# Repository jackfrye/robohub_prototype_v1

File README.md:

# robohub_prototype_v1
ATSAMA based board for command and control of future robotics systems

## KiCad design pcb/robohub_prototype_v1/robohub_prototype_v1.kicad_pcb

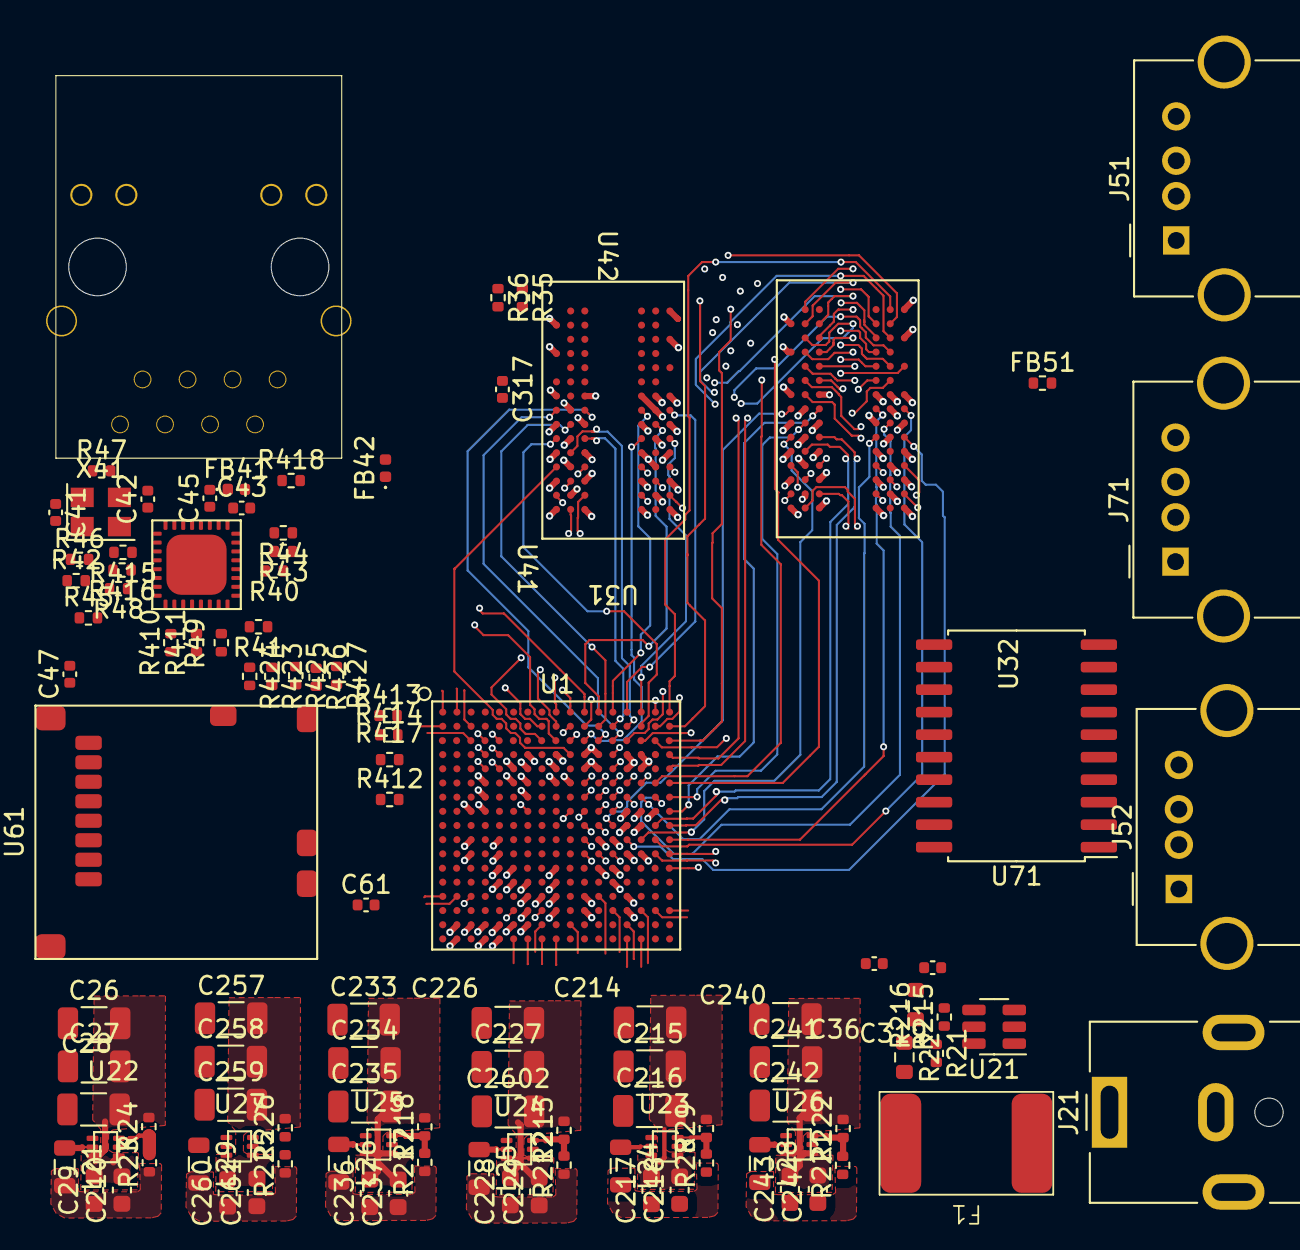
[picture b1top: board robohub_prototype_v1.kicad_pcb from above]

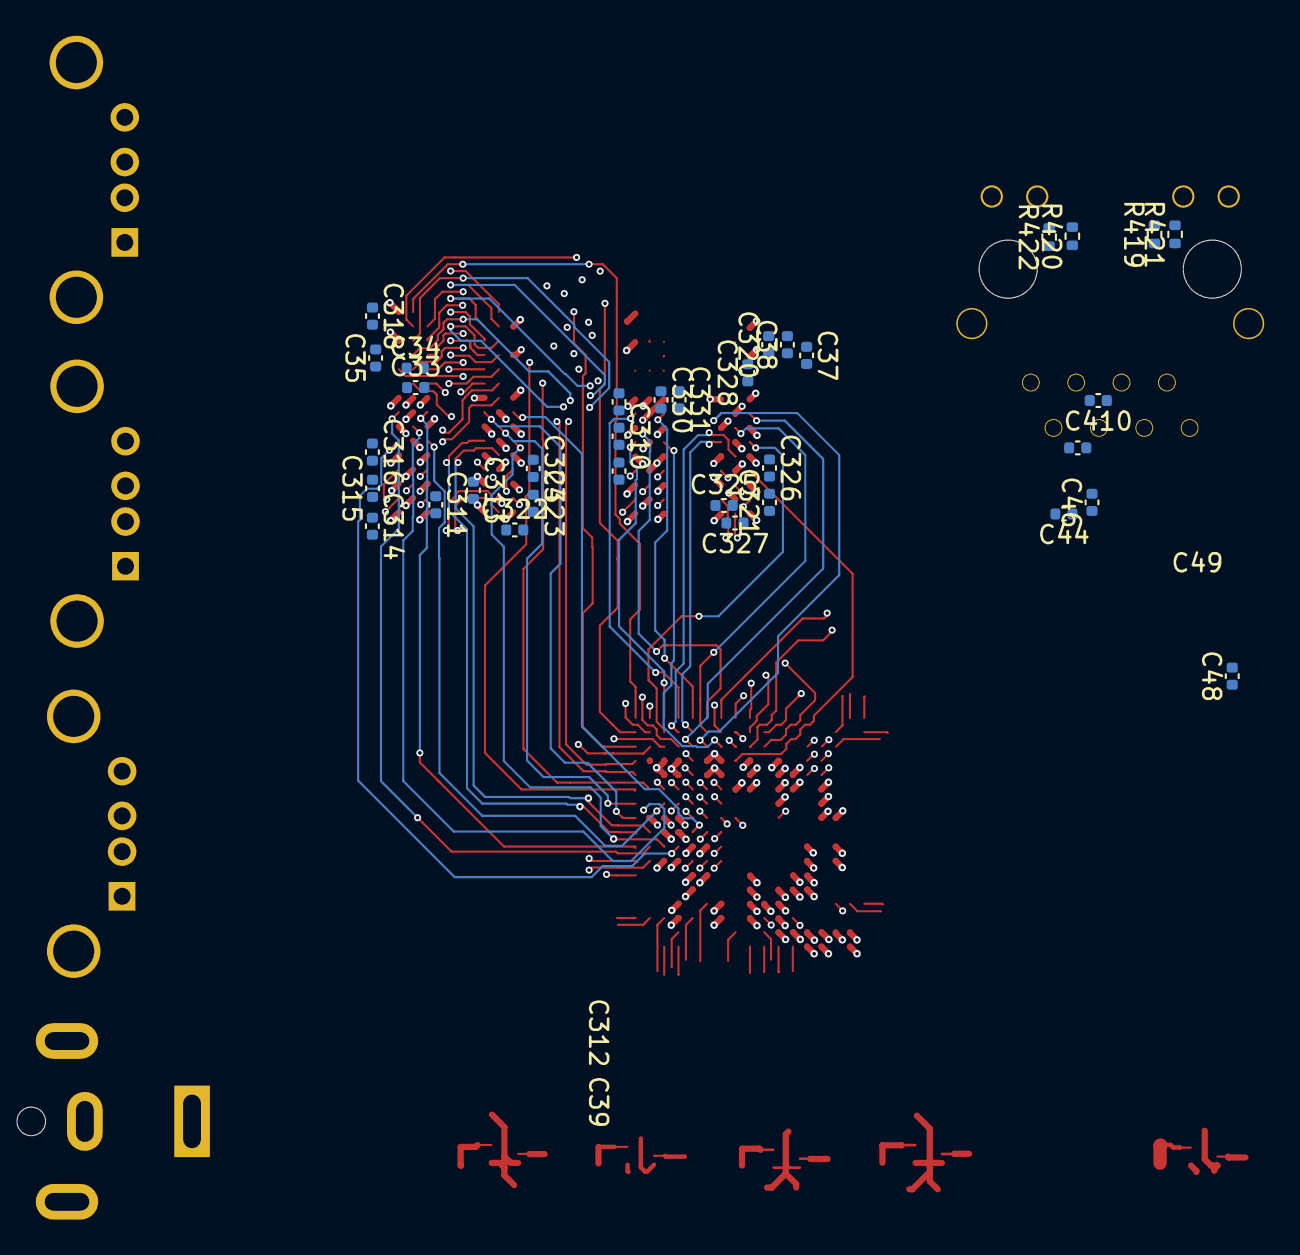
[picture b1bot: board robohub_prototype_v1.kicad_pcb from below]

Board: 10 copper layers, 144 parts (34 on the bottom side), 150 nets.

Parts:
C26, C27, C214, C215, C226, C227, C233, C234, C240, C241, C257, C258: 10u; C_1206_3216Metric
C28, C216, C235, C242, C259, C2602: 0.1u; C_1206_3216Metric
C29, C210, C217, C218, C228, C229, C236, C237, C243, C244, C260, C261: 22u; C_0603_1608Metric
C33, C38, C39, C44, C46, C48, C49, C310, C311, C312, C313, C320, C321, C322, C323, C324, C325, C330, C410: 100n; C_0402_1005Metric
C34, C314, C315, C316, C326, C327, C328: 1n; C_0402_1005Metric
C35, C45, C47, C61, C317: 10u; C_0402_1005Metric
C36, C37, C318, C319: 1u; C_0402_1005Metric
C41, C42: 22p; C_0402_1005Metric
C43: 2u2; C_0402_1005Metric
C331: 100nf; C_0402_1005Metric
F1: Fuse; 0ZCF0050FF2C
FB41, FB42: FerriteBead; D_0402_1005Metric
FB51: FerriteBead; R_0402_1005Metric
J21: Barrel_Jack_Switch_Pin3Ring; BarrelJack_CUI_PJ-063AH_Horizontal
J51, J52, J71: USB_A; USB_A_Molex_67643_Horizontal
L21, L24, L25: 2.2u; L_0805_2012Metric
L26, L28, L29: 1u; L_0805_2012Metric
R21, R23, R28, R35, R36, R212, R215: 100k; R_0402_1005Metric
R22, R216: 36.5k; R_0603_1608Metric
R24, R29, R213: 22.1k; R_0402_1005Metric
R40, R43, R44, R45, R46, R423, R424, R425, R426, R427: 10K; R_0402_1005Metric
R41, R42: 1K; R_0402_1005Metric
R47: DNP; R_0402_1005Metric
R48, R49, R410, R412, R413, R414, R415, R416, R417: 22; R_0402_1005Metric
R217, R218, R222, R226, R419, R420: 10k; R_0402_1005Metric
R221: 20k; R_0402_1005Metric
R225: 32k; R_0402_1005Metric
R411: 39; R_0402_1005Metric
R418: 6k4; R_0402_1005Metric
R421, R422: 510; R_0402_1005Metric
U1: ATSAMA5D27C
U21: LM3880; SOT-23-6
U22, U23, U24, U25, U26, U27: TPS564242DRL; TPS564247DRLR
U31, U32: W972GG6KB-25
U41: KSZ8081RNB
U42: SI-60110-F
U61: molex_5025700893
U71: MCP2200-I-SO; SOIC-20W_7.5x12.8mm_P1.27mm
X41: ECS-2520MV-xxx-xx; Oscillator_SMD_Abracon_ASE-4Pin_3.2x2.5mm

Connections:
5V: C26.1, C27.1, C28.1, C214.1, C215.1, C216.1, C226.1, C227.1, C233.1, C234.1, C235.1, C240.1, C241.1, C242.1, C257.1, C258.1, C259.1, C2602.1, F1.2, FB51.2, U21.1 (VCC), U21.3 (EN), U22.1 (VIN), U23.1 (VIN), U24.1 (VIN), U25.1 (VIN), U26.1 (VIN), U27.1 (VIN)
/DDR2_3/DDR_A0: U1.F12 (DDR_A0), U31.M8 (A0), U32.M8 (A0)
/DDR2_3/DDR_A1: U1.C17 (DDR_A1), U31.M3 (A1), U32.M3 (A1)
/DDR2_3/DDR_A2: U1.B17 (DDR_A2), U31.M7 (A2), U32.M7 (A2)
/DDR2_3/DDR_A3: U1.B16 (DDR_A3), U31.N2 (A3), U32.N2 (A3)
/DDR2_3/DDR_A4: U1.C16 (DDR_A4), U31.N8 (A4), U32.N8 (A4)
/DDR2_3/DDR_A5: U1.G14 (DDR_A5), U31.N3 (A5), U32.N3 (A5)
/DDR2_3/DDR_A6: U1.F14 (DDR_A6), U31.N7 (A6), U32.N7 (A6)
/DDR2_3/DDR_A7: U1.F11 (DDR_A7), U31.P2 (A7), U32.P2 (A7)
/DDR2_3/DDR_A8: U1.C14 (DDR_A8), U31.P8 (A8), U32.P8 (A8)
/DDR2_3/DDR_A9: U1.D13 (DDR_A9), U31.P3 (A9), U32.P3 (A9)
/DDR2_3/DDR_A10: U1.C15 (DDR_A10), U31.M2 (A10), U32.M2 (A10)
/DDR2_3/DDR_A11: U1.A16 (DDR_A11), U31.P7 (A11), U32.P7 (A11)
/DDR2_3/DDR_A12: U1.A17 (DDR_A12), U31.R2 (A12), U32.R2 (A12)
/DDR2_3/DDR_A13: U1.G11 (DDR_A13), U31.R8 (A13), U32.R8 (A13)
/DDR2_3/DDR_BA0: U1.H12 (DDR_BA0), U31.L2 (BA0), U32.L2 (BA0)
/DDR2_3/DDR_BA1: U1.H13 (DDR_BA1), U31.L3 (BA1), U32.L3 (BA1)
/DDR2_3/DDR_BA2: U1.F17 (DDR_DA2), U31.L1 (BA2), U32.L1 (BA2)
/DDR2_3/DDR_CAS: U1.G12 (DDR_CAS), U31.L7 (~CAS), U32.L7 (~CAS)
/DDR2_3/DDR_CKE: R36.1, U1.F16 (DDR_CKE), U31.K2 (CKE), U32.K2 (CKE)
/DDR2_3/DDR_CLK+: U1.E17 (DDR_CLK), U31.J8 (CK_P), U32.J8 (CK_P)
/DDR2_3/DDR_CLK-: U1.D17 (DDR_CLKN), U31.K8 (CK_N), U32.K8 (CK_N)
/DDR2_3/DDR_CS: U1.G13 (DDR_CS), U31.L8 (~CS), U32.L8 (~CS)
/DDR2_3/DDR_D0: U1.B12 (DDR_D0), U31.G8 (DQ0)
/DDR2_3/DDR_D1: U1.A12 (DDR_D1), U31.G2 (DQ1)
/DDR2_3/DDR_D2: U1.C12 (DDR_D2), U31.H7 (DQ2)
/DDR2_3/DDR_D3: U1.A13 (DDR_D3), U31.H3 (DQ3)
/DDR2_3/DDR_D4: U1.A14 (DDR_D4), U31.H1 (DQ4)
/DDR2_3/DDR_D5: U1.C13 (DDR_D5), U31.H9 (DQ5)
/DDR2_3/DDR_D6: U1.A15 (DDR_D6), U31.F1 (DQ6)
/DDR2_3/DDR_D7: U1.B15 (DDR_D7), U31.F9 (DQ7)
/DDR2_3/DDR_D8: U1.G17 (DDR_D8), U32.G8 (DQ0)
/DDR2_3/DDR_D9: U1.G16 (DDR_D9), U32.G2 (DQ1)
/DDR2_3/DDR_D10: U1.H17 (DDR_D10), U32.H7 (DQ2)
/DDR2_3/DDR_D11: U1.K17 (DDR_D11), U32.H3 (DQ3)
/DDR2_3/DDR_D12: U1.K16 (DDR_D12), U32.H1 (DQ4)
/DDR2_3/DDR_D13: U1.J13 (DDR_D13), U32.H9 (DQ5)
/DDR2_3/DDR_D14: U1.K14 (DDR_D14), U32.F1 (DQ6)
/DDR2_3/DDR_D15: U1.K15 (DDR_D15), U32.F9 (DQ7)
/DDR2_3/DDR_D16: U1.B8 (DDR_D16), U31.C8 (DQ8)
/DDR2_3/DDR_D17: U1.B9 (DDR_D17), U31.C2 (DQ9)
/DDR2_3/DDR_D18: U1.C9 (DDR_D18), U31.D7 (DQ10)
/DDR2_3/DDR_D19: U1.A9 (DDR_D19), U31.D3 (DQ11)
/DDR2_3/DDR_D20: U1.A10 (DDR_D20), U31.D1 (DQ12)
/DDR2_3/DDR_D21: U1.D10 (DDR_D21), U31.D9 (DQ13)
/DDR2_3/DDR_D22: U1.B11 (DDR_D22), U31.B1 (DQ14)
/DDR2_3/DDR_D23: U1.A11 (DDR_D23), U31.B9 (DQ15)
/DDR2_3/DDR_D24: U1.J12 (DDR_D24), U32.C8 (DQ8)
/DDR2_3/DDR_D25: U1.H10 (DDR_D25), U32.C2 (DQ9)
/DDR2_3/DDR_D26: U1.J11 (DDR_D26), U32.D7 (DQ10)
/DDR2_3/DDR_D27: U1.K11 (DDR_D27), U32.D3 (DQ11)
/DDR2_3/DDR_D28: U1.L13 (DDR_D28), U32.D1 (DQ12)
/DDR2_3/DDR_D29: U1.L11 (DDR_D29), U32.D9 (DQ13)
/DDR2_3/DDR_D30: U1.L12 (DDR_D30), U32.B1 (DQ14)
/DDR2_3/DDR_D31: U1.M17 (DDR_D31), U32.B9 (DQ15)
/DDR2_3/DDR_DQM0: U1.C11 (DDR_DQM0), U31.F3 (LDM)
/DDR2_3/DDR_DQM1: U1.G15 (DDR_DQM1), U32.F3 (LDM)
/DDR2_3/DDR_DQM2: U1.C8 (DDR_DQM2), U31.B3 (UDM)
/DDR2_3/DDR_DQM3: U1.H11 (DDR_DQM3), U32.B3 (UDM)
/DDR2_3/DDR_DQS0+: U1.B13 (DDR_DQS0), U31.F7 (LDQS_P)
/DDR2_3/DDR_DQS0-: U1.B14 (DDR_DQSN0), U31.E8 (NU/LDQS_N)
/DDR2_3/DDR_DQS1+: U1.J17 (DDR_DQS1), U32.F7 (LDQS_P)
/DDR2_3/DDR_DQS1-: U1.J16 (DDR_DQSN1), U32.E8 (NU/LDQS_N)
/DDR2_3/DDR_DQS2+: U1.C10 (DDR_DQS2), U31.B7 (UDQS_P)
/DDR2_3/DDR_DQS2-: U1.B10 (DDR_DQSN2), U31.A8 (NU/UDQS_N)
/DDR2_3/DDR_DQS3+: U1.L17 (DDR_DQS3), U32.B7 (UDQS_P)
/DDR2_3/DDR_DQS3-: U1.L16 (DDR_DQSN3), U32.A8 (NU/UDQS_N)
/DDR2_3/DDR_RAS: U1.F13 (DDR_RAS), U31.K7 (~RAS), U32.K7 (~RAS)
/DDR2_3/DDR_WE: U1.F15 (DDR_WE), U31.K3 (~WE), U32.K3 (~WE)
/Ethernet_MAC_4/CT1: C49.1, U42.4 (CT)
/Ethernet_MAC_4/CT2: C410.1, U42.5 (CT)
/Ethernet_MAC_4/ETH_COL_CONFI2: R40.2, U41.28 (COL/CONFIG0)
/Ethernet_MAC_4/ETH_CRS_CONFI1: R427.1, U41.29 (CRS/CONFIG1)
/Ethernet_MAC_4/ETH_LED0: R43.2, R419.2, U41.30 (LED0/NWAYEN), U42.11 (LED0)
/Ethernet_MAC_4/ETH_LED1: R44.2, R420.2, U41.31 (LED1/SPEED), U42.10 (LED1)
/Ethernet_MAC_4/ETH_RXC_BC: R411.1, U41.19 (RXC/B_CAST_OFF)
/Ethernet_MAC_4/ETH_RXD0_DUPLEX: R45.2, U41.16 (RXD0/DUPLEX)
/Ethernet_MAC_4/ETH_RXD1_PHYAD2: R48.1, R423.1, U41.15 (RXD1/PHYAD2)
/Ethernet_MAC_4/ETH_RXD2_PHYAD1: R426.1, U41.14 (RXD2/PHYAD1)
/Ethernet_MAC_4/ETH_RXD3_PHYAD0: R46.2, U41.13 (RXD3/PHYAD0)
/Ethernet_MAC_4/ETH_RXDIV_CONFIG2: R410.1, R425.1, U41.18 (RXDIV/CONFIG2)
/Ethernet_MAC_4/ETH_RXER_ISO: R49.1, R424.1, U41.20 (RXER/ISO)
/Ethernet_MAC_4/ETH_TX_D0: R413.1, U41.24 (TXD0)
/Ethernet_MAC_4/ETH_TX_D1: R412.1, U41.25 (TXD1)
/Ethernet_MAC_4/ETH_TX_EN: R414.1, U41.23 (TXEN)
/Ethernet_MAC_4/ETH_XI: C41.2, R47.1, U41.9 (XI), X41.1 (Tri-State)
/Ethernet_MAC_4/ETH_XO: C42.2, R47.2, U41.8 (X0), X41.3 (OUT)
/Ethernet_MAC_4/LED0_PWR: R421.2, U42.12 (LED0_PWR)
/Ethernet_MAC_4/LED1_PWR: R422.2, U42.9 (LED1_PWR)
/Ethernet_MAC_4/MDC: R416.1, U41.12 (MDC)
/Ethernet_MAC_4/MDIO: R42.2, R415.1, U41.11 (MDIO)
/Ethernet_MAC_4/REXT: R418.2, U41.10 (REXT)
/Ethernet_MAC_4/RXM: U41.4 (RXM), U42.6 (RD-)
/Ethernet_MAC_4/RXP: U41.5 (RXP), U42.3 (RD+)
/Ethernet_MAC_4/TXM: U41.6 (TXM), U42.2 (TD-)
/Ethernet_MAC_4/TXP: U41.7 (TXP), U42.1 (TD+)
/Ethernet_MAC_4/VDDA_3V3: C45.1, C46.1, FB41.1, U41.3 (VDDA_3V3)
/Ethernet_MAC_4/~INTRP_NAND: R41.2, R417.1, U41.21 (~INTRP/NAND)
/Power Managment_2/PS_GRP1_EN: R21.1, U21.6 (FLAG1)
/Power Managment_2/PS_GRP1_EN_DIV: R21.2, R22.1, U22.5 (EN), U23.5 (EN), U24.5 (EN), U26.5 (EN)
/Power Managment_2/PS_GRP2_EN: R215.1, U21.5 (FLAG2)
/Power Managment_2/PS_GRP2_EN_DIV: R215.2, R216.1, U25.5 (EN), U27.5 (EN)
/Power Managment_2/VCC_1_2_DDR_FB: R221.2, R222.1, U26.6 (FB)
/Power Managment_2/VCC_1_2_DDR_SW: L28.1, U26.2 (SW)
/Power Managment_2/VCC_1_2_FB: R217.2, R218.1, U25.6 (FB)
/Power Managment_2/VCC_1_2_SW: L26.1, U25.2 (SW)
/Power Managment_2/VCC_3_3_A_FB: R23.2, R24.1, U22.6 (FB)
/Power Managment_2/VCC_3_3_A_SW: L21.1, U22.2 (SW)
/Power Managment_2/VCC_3_3_B_FB: R28.2, R29.1, U23.6 (FB)
/Power Managment_2/VCC_3_3_B_SW: L24.1, U23.2 (SW)
/Power Managment_2/VCC_3_3_C_FB: R212.2, R213.1, U24.6 (FB)
/Power Managment_2/VCC_3_3_C_SW: L25.1, U24.2 (SW)
/UART_7/D+: J71.3 (D+), U71.19 (D+)
/UART_7/D-: J71.2 (D-), U71.18 (D-)
/UART_7/VDD: J71.1 (VBUS), U71.1 (VDD), U71.13 (CTS)
CH_GND: FB42.1, U42.8 (CH_GND), U42.13 (CH_GND), U42.14 (CH_GND)
DDR_VREF: C33.1, C34.1, C330.1, C331.1, U1.D16 (DDR_VREF), U1.H16 (DDR_VREF), U31.J2 (VREF), U32.J2 (VREF)
GND: C26.2, C27.2, C28.2, C29.2, C33.2, C34.2, C35.2, C36.2, C37.2, C38.2, C39.2, C41.1, C42.1, C43.2, C44.2, C45.2, C46.2, C47.2, C48.2, C49.2, C61.2, C210.2, C214.2, C215.2, C216.2, C217.2, C218.2, C226.2, C227.2, C228.2, C229.2, C233.2, C234.2, C235.2, C236.2, C237.2, C240.2, C241.2, C242.2, C243.2, C244.2, C257.2, C258.2, C259.2, C260.2, C261.2, C310.2, C311.2, C312.2, C313.2, C314.2, C315.2, C316.2, C317.2, C318.2, C319.2, C320.2, C321.2, C322.2, C323.2, C324.2, C325.2, C326.2, C327.2, C328.2, C330.2, C331.2, C410.2, C2602.2, FB42.2, J21.2, J51.4 (GND), J52.4 (GND), J71.4 (GND), R22.2, R24.2, R29.2, R36.2, R213.2, R216.2, R218.2, R222.2, R226.2, R418.1, R423.2, R424.2, R425.2, R426.2, R427.2, U1.D14 (GNDIODDR), U1.E7 (GNDCORE), U1.E9 (GNDCORE), U1.E11 (GNDIODDR), U1.E12 (GNDIODDR), U1.E14 (GNDIODDR), U1.F6 (GNDIOP0), U1.F9 (GNDIOP2), U1.G4 (GNDISC), U1.G7 (GNDIOP0), U1.H4 (GNDCORE), U1.H14 (GNDIODDR), U1.J14 (GNDIODDR), U1.K5 (GNDANA), U1.K12 (GNDCORE), U1.L3 (GNDANA), U1.L14 (GNDIODDR), U1.M5 (GNDCORE), U1.M9 (GNDCORE), U1.M13 (GNDIOP1), U1.N6 (GNDBU), U1.P9 (GNDUTMII), U1.P14 (GNDIOP1), U1.R7 (GNDUTMIC), U1.R11 (GNDSDMMC), U1.T4 (GNDAUDIOPLL), U1.T5 (GNDPLL), U1.T6 (GNDOSC), U1.U5 (GNDPLLA), U21.2 (GND), U22.3 (GND), U22.4 (AGND), U23.3 (GND), U23.4 (AGND), U24.3 (GND), U24.4 (AGND), U25.3 (GND), U25.4 (AGND), U26.3 (GND), U26.4 (AGND), U27.3 (GND), U27.4 (AGND), U31.A3 (VSS1), U31.A7 (VSSQ1), U31.B2 (VSSQ2), U31.B8 (VSSQ3), U31.D2 (VSSQ4), U31.D8 (VSSQ5), U31.E3 (VSS2), U31.E7 (VSSQ6), U31.F2 (VSSQ7), U31.F8 (VSSQ8), U31.H2 (VSSQ9), U31.H8 (VSSQ10), U31.J3 (VSS3), U31.J7 (VSSDL), U31.N1 (VSS4), U31.P9 (VSS5), U32.A3 (VSS1), U32.A7 (VSSQ1), U32.B2 (VSSQ2), U32.B8 (VSSQ3), U32.D2 (VSSQ4), U32.D8 (VSSQ5), U32.E3 (VSS2), U32.E7 (VSSQ6), U32.F2 (VSSQ7), U32.F8 (VSSQ8), U32.H2 (VSSQ9), U32.H8 (VSSQ10), U32.J3 (VSS3), U32.J7 (VSSDL), U32.N1 (VSS4), U32.P9 (VSS5), U41.1 (GND), U41.33 (PADDLE), U61.6 (VSS), U61.11 (SHELL), U61.12 (SHELL), U61.13 (SHELL), U61.14 (SHELL), U71.20 (VSS), X41.2 (GND), X41.4 (VDD)
unnamed: R35.2, U1.E16 (DDR_RESETN)
unnamed: R225.2, R226.1, U27.6 (FB)
unnamed: L29.1, U27.2 (SW)
PA18_SD_DAT0: U1.U14 (PA18), U61.7 (DAT0)
PA19_SD_DAT1: U1.T14 (PA19), U61.8 (DAT1)
PA20_SD_DAT2: U1.P12 (PA20), U61.1 (DAT2)
PA21_SD_DAT3: U1.R13 (PA21), U61.2 (CD/DAT3)
PB14_ETH_RXC_BC: R411.2, U1.C5 (PB14)
PB15_ETH_TX_EN: R414.2, U1.H7 (PB15)
PB16_ETH_RXDIV_CONFIG2: R410.2, U1.D5 (PB16)
PB17_ETH_RXER_ISO: R49.2, U1.C4 (PB17)
PB19_ETH_RXD1_PHYAD2: R48.2, U1.D4 (PB19)
PB20_ETH_TX_D0: R413.2, U1.B3 (PB20)
PB21_ETH_TX_D1: R412.2, U1.A2 (PB21)
PB22_MDC: R416.2, U1.C3 (PB22)
PB23_MDIO: R415.2, U1.A1 (PB23)
PB24_~INTRP_NAND: R417.2, U1.E5 (PB24)
PB26_UART_RX: U1.E4 (PB26), U71.12 (RX)
PB27_UART_TX: U1.B1 (PB27), U71.10 (TX)
SD_VDD: C61.1, C217.1, C218.1, L24.2, R28.1, U1.E6 (VDDIOP0), U1.F4 (VDDISC), U1.F7 (VDDIOP0), U1.F10 (VDDIOP2), U1.N13 (VDDIOP1), U1.P11 (VDDSDMMC), U1.R14 (VDDIOP1), U1.U2 (NRST), U61.4 (VDD)
USBA_5V: FB51.1, J51.1 (VBUS)
USBA_DM: J51.2 (D-), U1.R8 (HHSDMA)
USBA_DP: J51.3 (D+), U1.T8 (HHSDPA)
USBB_DM: J52.2 (D-), U1.U9 (HHSDMB)
USBB_DP: J52.3 (D+), U1.U8 (HHSDPB)
VCC: F1.1, J21.1
VCC_1_2: C43.1, C44.1, C236.1, C237.1, L26.2, R217.1, U1.D7 (VDDCORE), U1.D9 (VDDCORE), U1.H3 (VDDCORE), U1.K13 (VDDCORE), U1.N5 (VDDCORE), U1.N9 (VDDCORE), U1.P7 (VDDUTMIC), U1.R9 (VDDHSIC), U41.2 (VDD_1V2)
VCC_1_8_DDR: C35.1, C36.1, C37.1, C38.1, C39.1, C243.1, C244.1, C310.1, C311.1, C312.1, C313.1, C314.1, C315.1, C316.1, C317.1, C318.1, C319.1, C320.1, C321.1, C322.1, C323.1, C324.1, C325.1, C326.1, C327.1, C328.1, L28.2, R35.1, R221.1, U1.D11 (VDDIODDR), U1.D12 (VDDIODDR), U1.D15 (VDDIODDR), U1.E15 (VDDIODDR), U1.H15 (VDDIODDR), U1.J15 (VDDIODDR), U1.L15 (VDDIODDR), U31.A1 (VDD1), U31.A9 (VDDQ1), U31.C1 (VDDQ2), U31.C3 (VDDQ3), U31.C7 (VDDQ4), U31.C9 (VDDQ5), U31.E1 (VDD2), U31.E9 (VDDQ6), U31.G1 (VDDQ7), U31.G3 (VDDQ8), U31.G7 (VDDQ9), U31.G9 (VDDQ10), U31.J1 (VDDL), U31.J9 (VDD3), U31.M9 (VDD4), U31.R1 (VDD5), U32.A1 (VDD1), U32.A9 (VDDQ1), U32.C1 (VDDQ2), U32.C3 (VDDQ3), U32.C7 (VDDQ4), U32.C9 (VDDQ5), U32.E1 (VDD2), U32.E9 (VDDQ6), U32.G1 (VDDQ7), U32.G3 (VDDQ8), U32.G7 (VDDQ9), U32.G9 (VDDQ10), U32.J1 (VDDL), U32.J9 (VDD3), U32.M9 (VDD4), U32.R1 (VDD5)
VCC_2_5: C260.1, C261.1, L29.2, R225.1, U1.M12 (VDDFUSE)
VCC_3_3_C: C228.1, C229.1, L25.2, R212.1, U1.K3 (VDDANA), U1.L5 (VDDANA), U1.M6 (ADVREF), U1.P8 (VDDUTMII)
VDDBU: C29.1, C210.1, L21.2, R23.1, U1.N7 (VDDBU), U1.T2 (JTAGSEL)
VDDIOP0: C47.1, C48.1, FB41.2, R40.1, R41.1, R42.1, R43.1, R44.1, R45.1, R46.1, R419.1, R420.1, R421.1, R422.1

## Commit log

2024-03-03 Initial commit of PCB files
2024-03-22 Update project to Kicad8. Update schematic, start fanning out BGA on PCB
2024-04-06 Update paths to footprint libraries. Begin adding footprints for PDN resistors. Create master BOM
2024-04-12 Begin PDN circuit design/BOM/layout
2024-04-14 Update paths for footprints top adjacent lib directory at above clone. Finish basic regulator layout/BOM. Link 3d STEPs into model. Rearrangle layout
2024-04-25 Add fuse to PCB design
2024-04-29 Update schematic and pcb with net groups for routing DDR2
2024-04-29 Small updates to ACC signals for DDR2
2024-05-02 Update build up
2024-05-05 Update PCB with copy for fanout length matching
2024-05-09 Update pcb with decoupling, updated winbond ddr footprint. added some decoupling caps
2024-05-14 Start placing and moving decoupling caps
2024-05-16 Add changes for docoupling capacitors
2024-05-20 Start routing ddr2
2024-05-24 Attempts to route ddr
2024-05-28 Attempts to route the ddr2
2024-05-31 Effort at routing ACC
2024-06-04 Update schematic for byte swap; change ddr2 layout; begin reroute of ddr2
2024-06-07 Moved some stuff around, tried a route
2024-06-11 Update PCB route to match example design
2024-06-18 Update PCB routing of DDR2
2024-06-28 Started routing inner layer ddr2
2024-07-01 Updates to DDR2 routing on inner layers
2024-07-04 Addd updated DDR2 routingg
2024-07-08 Add updated PCB routing for data byte lanes
2024-07-12 Routing data bytes
2024-07-17 Updates to routing second byte lane
2024-07-17 Rip up to begin reroute
2024-07-19 Routed 3/4 data bytes, no length matching
2024-07-26 Routing data byte groups and half of address
2024-07-29 Update footprint assignment. begin laying out ethernet
